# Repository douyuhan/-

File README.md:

README:smile:
===========================
give you a  :star:    
欢迎来玩呀！:kissing_closed_eyes:

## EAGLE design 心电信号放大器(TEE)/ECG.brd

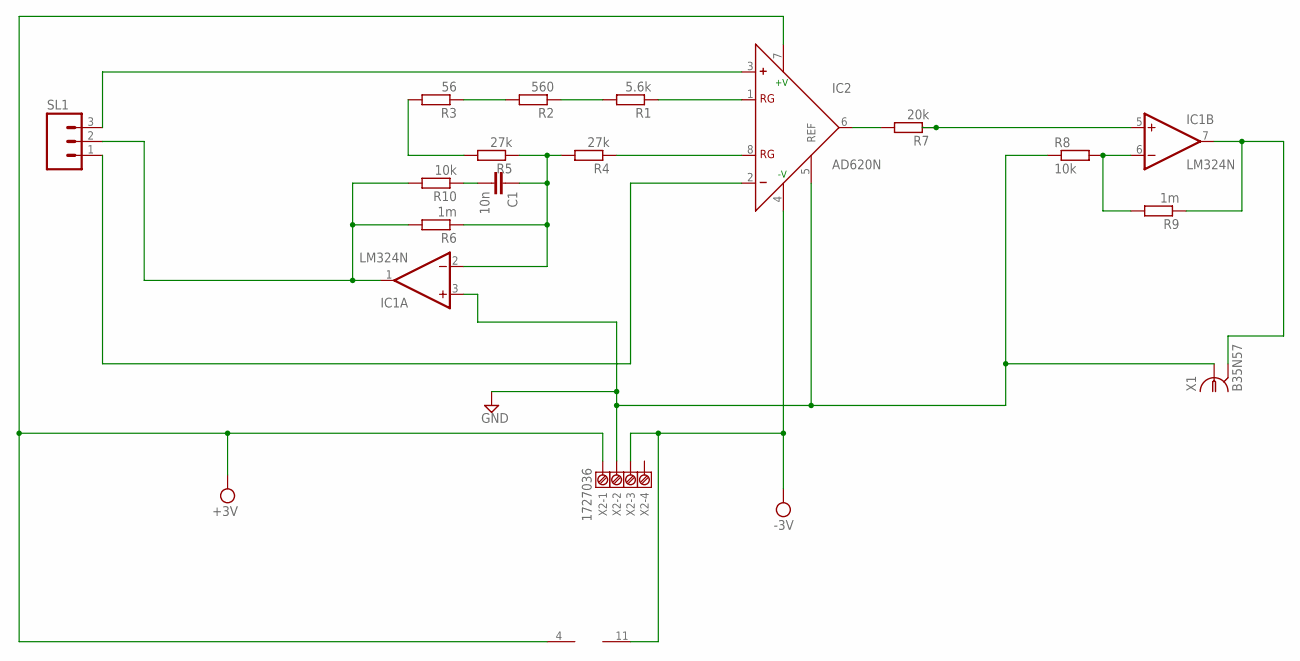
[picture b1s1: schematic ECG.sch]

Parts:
C1: 10n; C025-024X044
IC1: LM324N; DIL14
IC2: AD620N; DIL08
R1: 5.6k; 0204/7
R2: 560; 0204/7
R3: 56; 0204/7
R4, R5: 27k; 0204/7
R6, R9: 1m; 0204/7
R7: 20k; 0204/7
R8, R10: 10k; 0204/7
SL1: MA03; 03P
X1: B35N57
X2: 1727036

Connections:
GND: IC1.3 (+IN), IC2.5 (REF), R8.1, X1.1, X2.2
unnamed: IC1.5 (+IN), R7.1
unnamed: R1.2, R2.1
unnamed: IC2.8 (RG), R4.1
unnamed: IC2.1 (RG), R1.1
unnamed: IC2.6 (OUT), R7.2
unnamed: IC1.1 (OUT), R6.2, R10.2, SL1.2
unnamed: R2.2, R3.1
unnamed: R3.2, R5.2
unnamed: IC2.2 (-), SL1.1
unnamed: IC2.3 (+), SL1.3
unnamed: C1.2, R10.1
unnamed: C1.1, IC1.2 (-IN), R4.2, R5.1, R6.1
unnamed: IC1.6 (-IN), R8.2, R9.2
unnamed: IC1.7 (OUT), R9.1, X1.2, X1.3 (2), X1.4 (2), X1.5 (2)
VCC: IC1.4 (V+), IC2.7 (+V), X2.1
VEE: IC1.11 (V-), IC2.4 (-V), X2.3

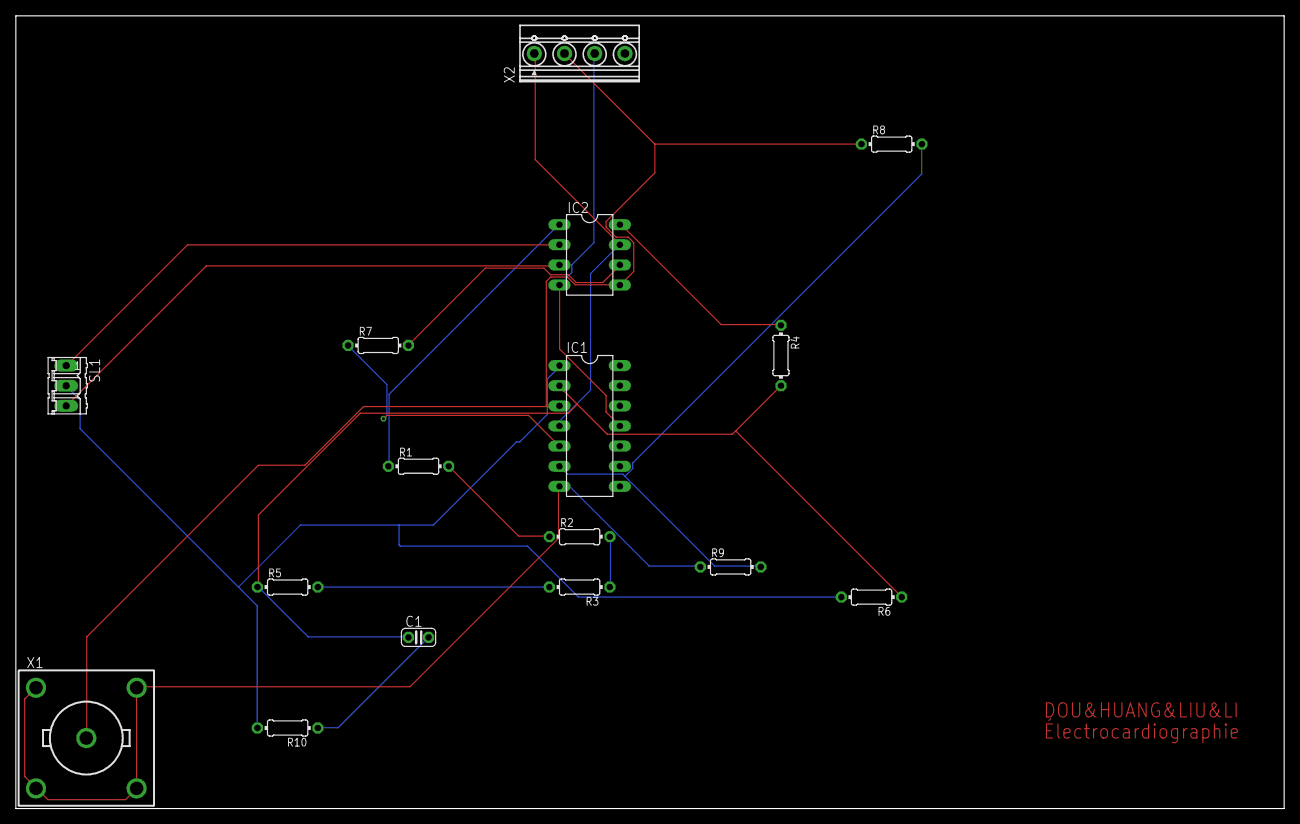
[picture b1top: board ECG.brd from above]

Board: 2 copper layers, 160.0 x 100.0 mm, 16 parts (0 on the bottom side), 17 nets.

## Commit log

2022-09-16 Update README.md
    小 豆豆
